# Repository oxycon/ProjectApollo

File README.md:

# ProjectApollo
This Github repository contains Designs/docs/software/PCB for Project Apollo (open source oxygen concentrator)

For more context behind the history/goals/motivation for this project please see our coverage in Helpful Engineering blog: 
- https://www.helpfulengineering.org/projects-news/project-spotlight-apollo-oxygen-concentrator/  

<b style='color:red'>Update</b>: check out our  presentation at RespiCon 2021! 
- https://github.com/oxycon/ProjectApollo/blob/master/docs/Project%20Apollo%20RespiCon%20v11.pdf

## Apollo v2 build instructions
- https://github.com/oxycon/ProjectApollo/blob/master/prototypes/Apollo%20v2/docs/Building%20instructions%20-%20prototype%20v2.pdf 

## Why
- Ventilators need oxygen! (typical FiO2 0.4 … 0.9)
- Oxygen generation is a big problem in developing countries. 
  - No established infrastructure. 
  - Oxygen bottles are expensive
- People are already looking at alternative (local) ways for producing oxygen
## What 
- Goal of the Apollo prototype = enabling people around the world to build the prototype as fast as possible
- Focus = Simplicity and speed of build 
- Final goal = Enable people to iterate and publish their own designs in the community
## How
- Follow the published build documentation
- Buy/source the materials (check out the BOM)
- Build the prototype
- Validate O2 concentration and flow. Use a good O2 and flow sensor. 
- Think about risk analysis and assessment: template for Apollo-derived design
- Document and iterate your own design. Publish your findings to the community! 

## Target 
- Output medical grade Oxygen ideally at 93% 
- Flow rate of 1-20 liters per minute (5 l/m being standard for oxygen therapy)

## Building instructions (prototype v2)
- Achieves O2 concentration out of the box: around 45% @ 5 liters/min (enough for less-critical ventilator use cases)
- Instructables-style (step-by-step) build instructions: https://github.com/oxycon/ProjectApollo/blob/master/prototypes/Apollo%20v2/docs/Building%20instructions%20-%20prototype%20v2.pdf 
- Bill of materials: https://github.com/oxycon/ProjectApollo/tree/master/prototypes/Apollo%20v2/BOM 

## Youtube videos
- Prototype v1 (old): https://www.youtube.com/playlist?list=PL34ykrB-qW7VGt1Hwd10Zb3s1eCDftkK8 
- Prototype v2 (latest): https://www.youtube.com/playlist?list=PL34ykrB-qW7X6d74_VnCFfBaVkm8pQXZK

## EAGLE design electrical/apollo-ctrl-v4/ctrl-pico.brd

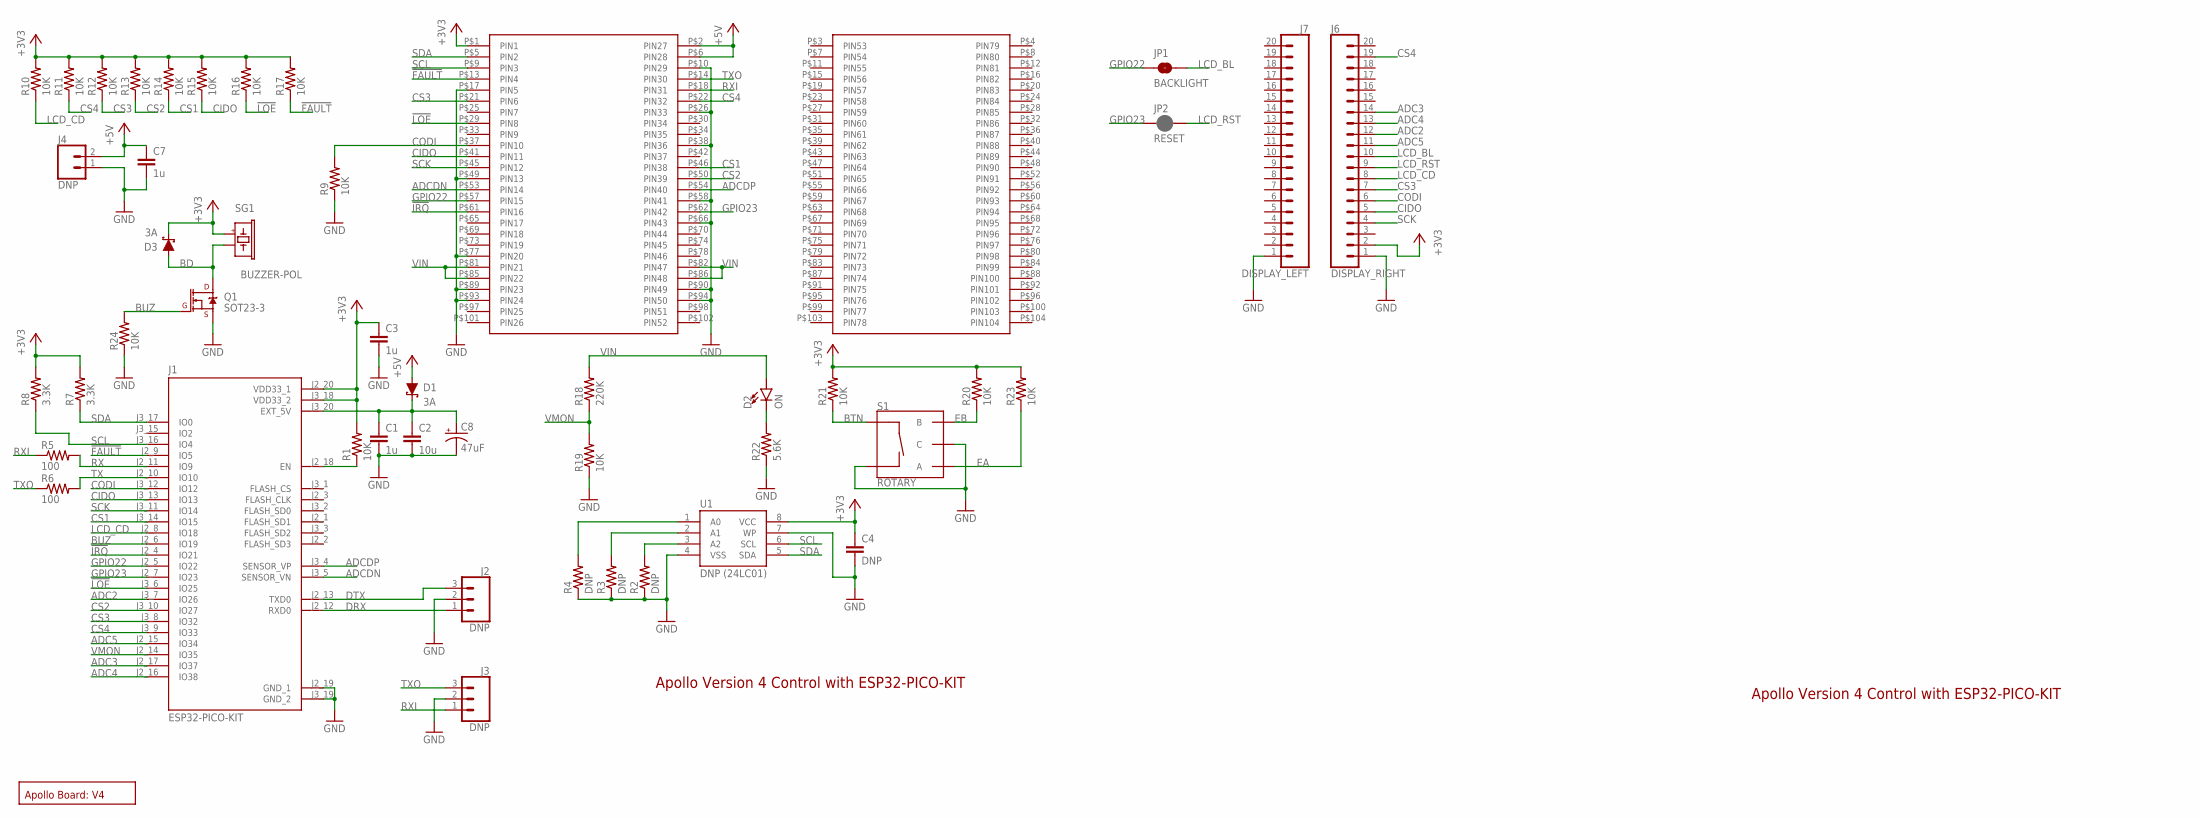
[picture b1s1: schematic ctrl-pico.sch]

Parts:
C1, C3, C7: 1u; 0805
C2: 10u; 0805
C4: DNP; 0805
C8: 47uF; PANASONIC_D
D1, D3: 3A; SMA-DIODE
D2: ON; LED-0603
J1: ESP32-PICO-KIT; XCVR_ESP32-PICO-KIT
J2, J3: DNP; 1X03
J4: DNP; 1X02
J6: DISPLAY_RIGHT; 1X20
J7: DISPLAY_LEFT; 1X20
JP1: BACKLIGHT; SMT-JUMPER_2_NO_NO-SILK
JP2: RESET; SMT-JUMPER_2_NC_PASTE_NO-SILK
Q1: SOT23-3
R1, R9, R10, R11, R12, R13, R14, R15, R16, R17, R19, R20, R21, R23, R24: 10K; 0805
R2, R3, R4: DNP; 0805
R5, R6: 100; 0805
R7, R8: 3.3K; 0805
R18: 220K; 0805
R22: 5.6K; 0805
S1: ROTARY; ROTARY_ENC_PLAIN
SG1: BUZZER-POL; BUZZER-SMT-4
U1: DNP (24LC01); SO08
U$1: PC104_CONNECTOR
U$2: BOARD_TEMPLATE1; BOARD_TEMPLATE

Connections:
!FAULT!: J1.J2_9 (IO5), R17.1, U$1.P$13 (PIN4)
!IRQ!: J1.J2_4 (IO21), U$1.P$61 (PIN16)
!LOE!: J1.J3_6 (IO25), R16.1, U$1.P$29 (PIN8)
+3V3: C3.1, C4.1, D3.C, J1.J2_20 (VDD33_1), J1.J3_18 (VDD33_2), J6.2, R1.2, R7.2, R8.2, R10.2, R11.2, R12.2, R13.2, R14.2, R15.2, R16.2, R17.2, R20.2, R21.2, R23.2, SG1.BP, U1.8 (VCC), U$1.P$1 (PIN1)
+5V: C7.1, D1.A, J4.2, U$1.P$2 (PIN27), U$1.P$6 (PIN28)
A0: R4.2, U1.1 (A0)
A1: R3.2, U1.2 (A1)
A2: R2.2, U1.3 (A2)
ADC2: J1.J3_7 (IO26), J6.12
ADC3: J1.J2_17 (IO37), J6.14
ADC4: J1.J2_16 (IO38), J6.13
ADC5: J1.J2_15 (IO34), J6.11
ADCDN: J1.J3_5 (SENSOR_VN), U$1.P$53 (PIN14)
ADCDP: J1.J3_4 (SENSOR_VP), U$1.P$54 (PIN40)
BD: D3.A, Q1.3 (D), SG1.BM (N)
BTN: R21.1, S1.SW+
BUZ: J1.J2_6 (IO19), Q1.1 (G), R24.2
CIDO: J1.J3_13 (IO13), J6.5, R15.1, U$1.P$41 (PIN11)
CODI: J1.J3_12 (IO12), J6.6, R9.2, U$1.P$37 (PIN10)
CS1: J1.J3_14 (IO15), R14.1, U$1.P$46 (PIN38)
CS2: J1.J3_10 (IO27), R13.1, U$1.P$50 (PIN39)
CS3: J1.J3_8 (IO32), J6.7, R12.1, U$1.P$21 (PIN6)
CS4: J1.J3_9 (IO33), J6.19, R11.1, U$1.P$22 (PIN32)
DRX: J1.J2_12 (RXD0), J2.1
DTX: J1.J2_13 (TXD0), J2.3
EA: R23.1, S1.A
EB: R20.1, S1.B
EN: J1.J2_18 (EN), R1.1
GND: C1.2, C2.2, C3.2, C4.2, C7.2, C8.-, J1.J2_19 (GND_1), J1.J3_19 (GND_2), J2.2, J3.2, J4.1, J6.1, J7.1, Q1.2 (S), R2.1, R3.1, R4.1, R9.1, R19.1, R22.1, R24.1, S1.C, S1.SW-, U1.4 (VSS), U1.7 (WP), U$1.P$10 (PIN29), U$1.P$17 (PIN5), U$1.P$26 (PIN33), U$1.P$38 (PIN36), U$1.P$49 (PIN13), U$1.P$58 (PIN41), U$1.P$66 (PIN43), U$1.P$77 (PIN20), U$1.P$89 (PIN23), U$1.P$90 (PIN49), U$1.P$93 (PIN24), U$1.P$94 (PIN50)
GPIO22: J1.J2_5 (IO22), JP1.1, U$1.P$57 (PIN15)
GPIO23: J1.J2_7 (IO23), JP2.1, U$1.P$62 (PIN42)
LCD_BL: J6.10, JP1.2
LCD_CD: J1.J2_8 (IO18), J6.8, R10.1
LCD_RST: J6.9, JP2.2
RX: J1.J2_11 (IO9), R5.2
RXI: J3.1, R5.1, U$1.P$18 (PIN31)
SCK: J1.J3_11 (IO14), J6.4, U$1.P$45 (PIN12)
SCL: J1.J3_16 (IO4), R8.1, U1.6 (SCL), U$1.P$9 (PIN3)
SDA: J1.J3_17 (IO0), R7.1, U1.5 (SDA), U$1.P$5 (PIN2)
TX: J1.J2_10 (IO10), R6.2
TXO: J3.3, R6.1, U$1.P$14 (PIN30)
USB5V: C1.1, C2.1, C8.+, D1.C, J1.J3_20 (EXT_5V)
VIN: D2.A, R18.2, U$1.P$81 (PIN21), U$1.P$82 (PIN47), U$1.P$85 (PIN22), U$1.P$86 (PIN48)
VLED: D2.C, R22.2
VMON: J1.J2_14 (IO35), R18.1, R19.2

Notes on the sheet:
Apollo Version 4 Control with ESP32-PICO-KIT

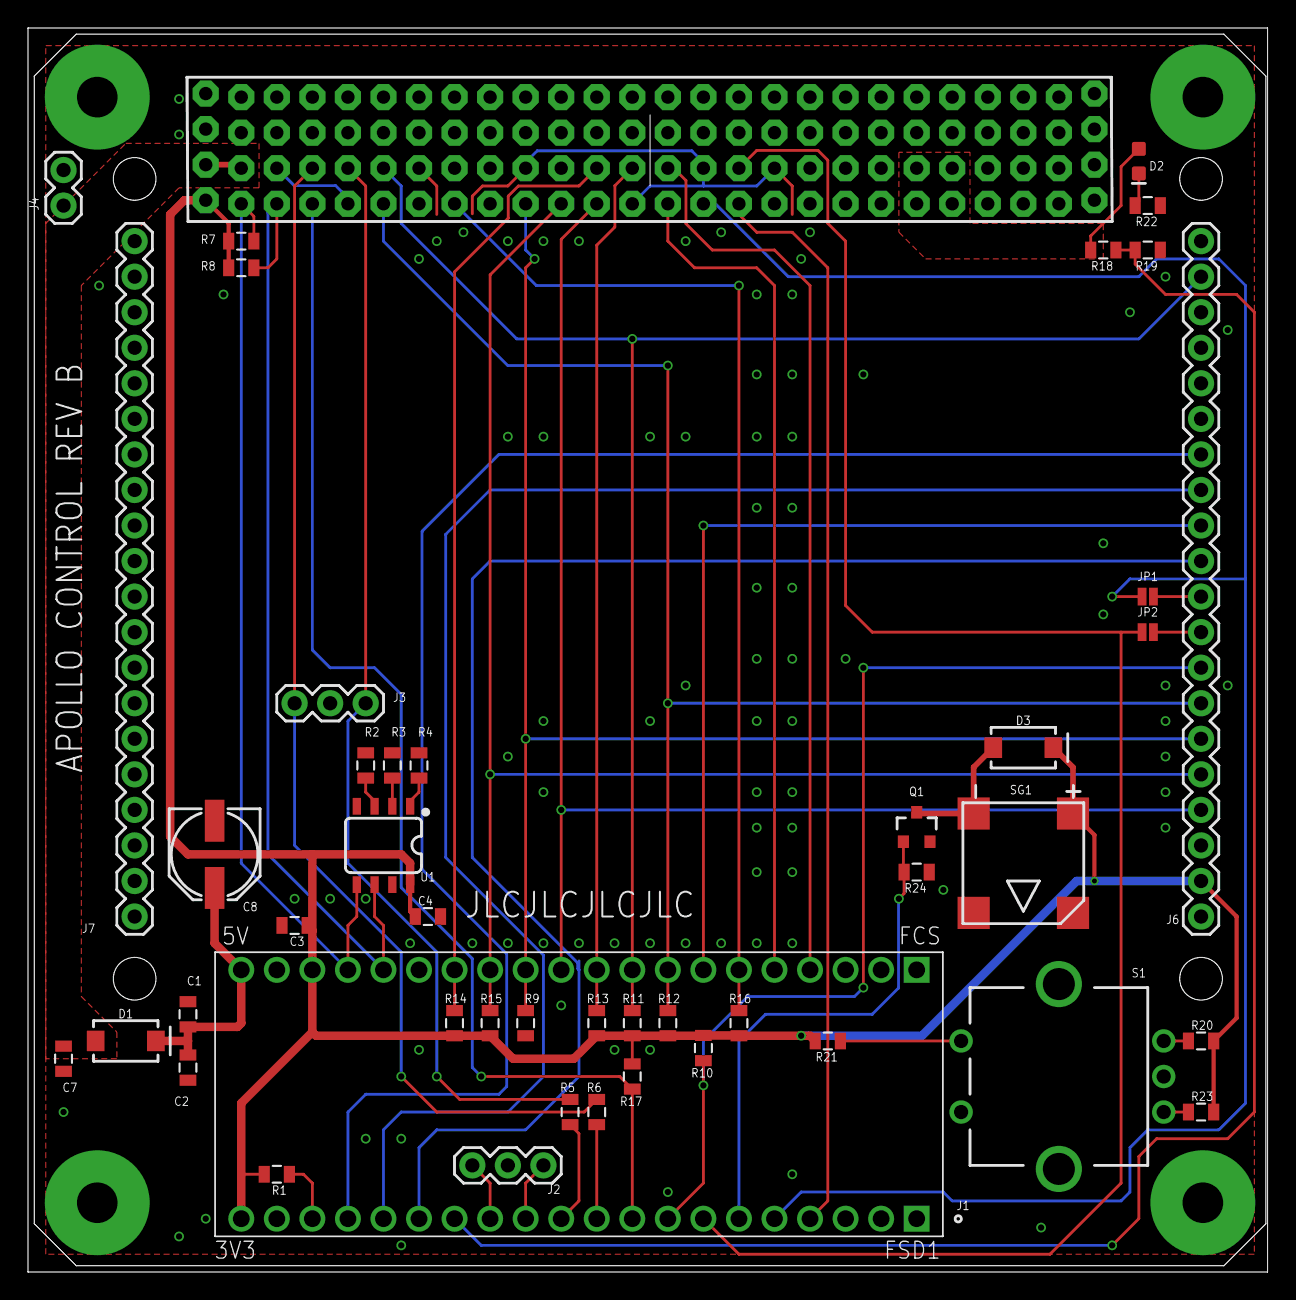
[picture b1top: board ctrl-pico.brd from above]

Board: 2 copper layers, 88.6 x 88.9 mm, 47 parts (0 on the bottom side), 45 nets.

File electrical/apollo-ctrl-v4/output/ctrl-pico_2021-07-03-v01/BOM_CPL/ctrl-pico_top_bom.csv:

Comment,Designator,Footprint,LCSC Part #
1u,C1 C3 C7,0805,
3.3K,R7 R8,0805,
3A,D1 D3,SMA-DIODE,
5.6K,R22,0805,
10K,R1 R9 R10 R11 R12 R13 R14 R15 R16 R17 R19 R20 R21 R23 R24,0805,
10u,C2,0805,
47uF,C8,PANASONIC_D,C134878
100,R5 R6,0805,
220K,R18,0805,
BACKLIGHT,JP1,SMT-JUMPER_2_NO_NO-SILK,
BUZZER-POL,SG1,BUZZER-SMT-4,
DNP,C4 R2 R3 R4,0805,
DNP (24LC01),U1,SO08,
ON,D2,LED-0603,
RESET,JP2,SMT-JUMPER_2_NC_PASTE_NO-SILK,
SOT23-3,Q1,SOT23-3,

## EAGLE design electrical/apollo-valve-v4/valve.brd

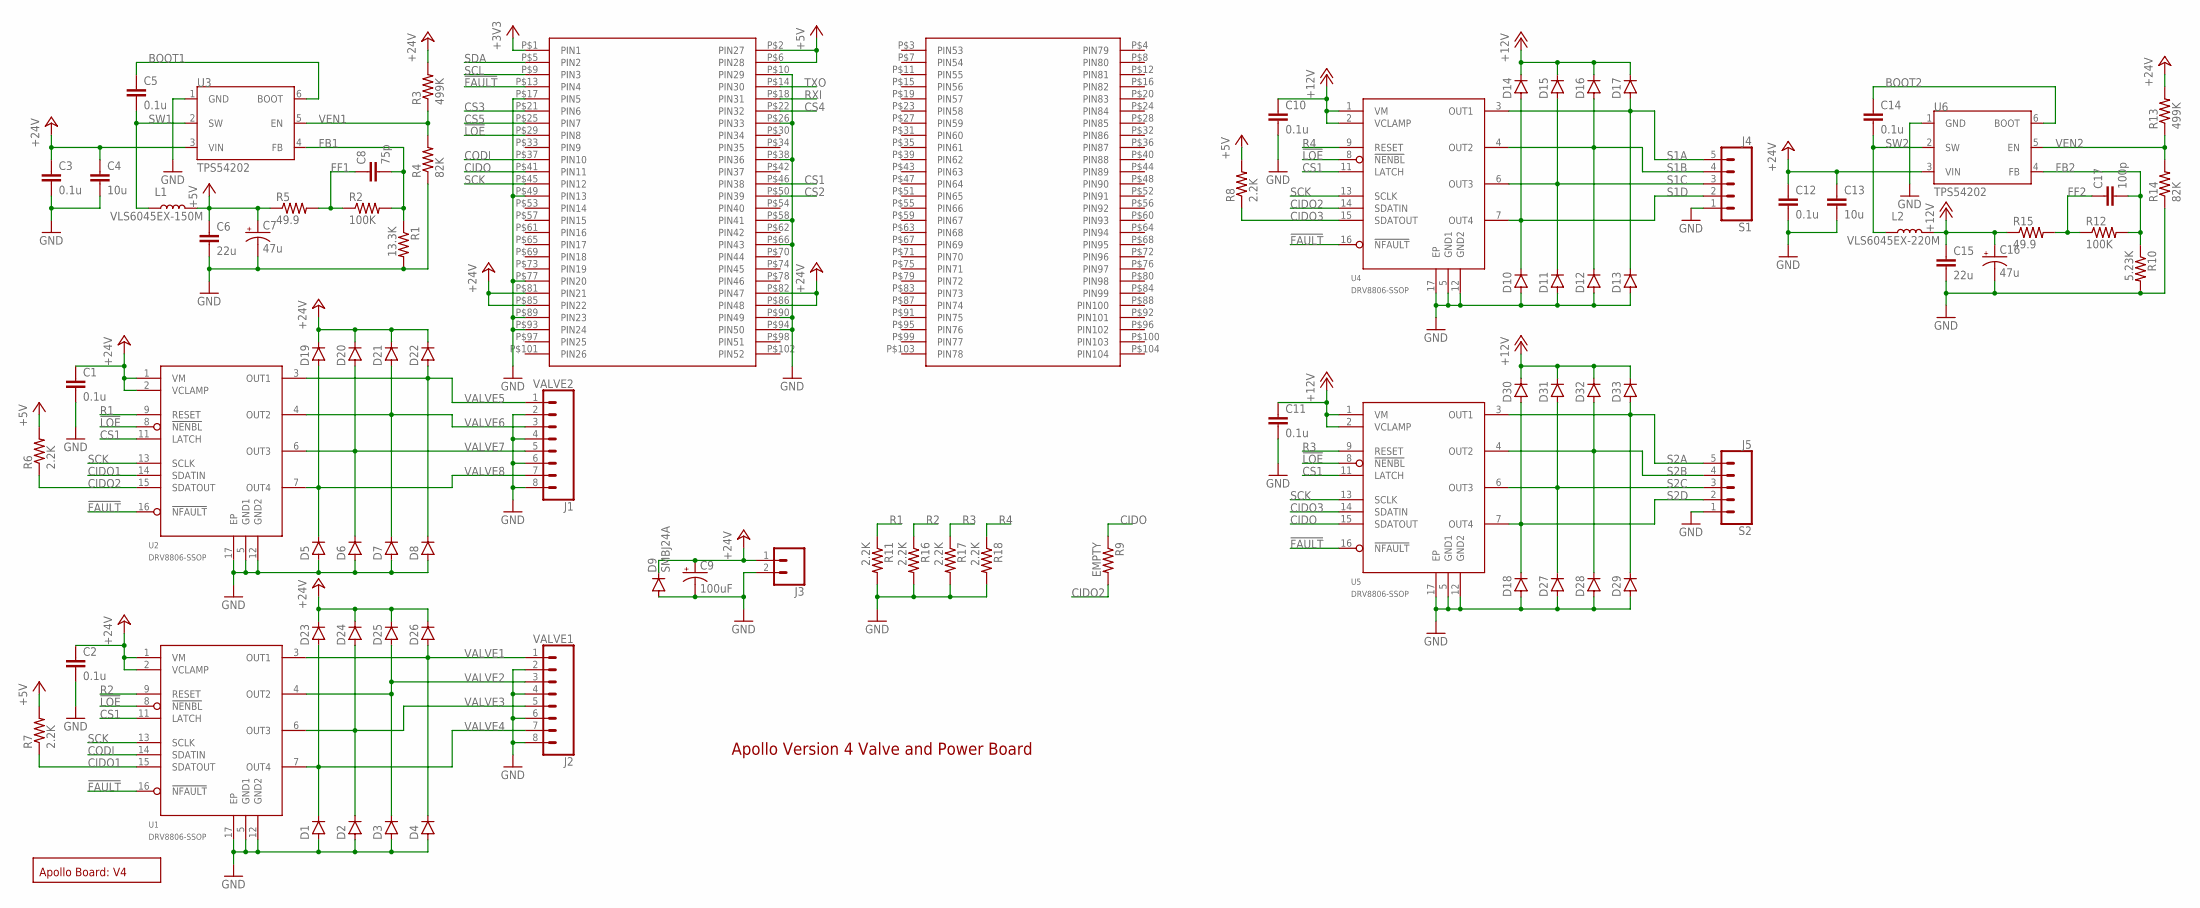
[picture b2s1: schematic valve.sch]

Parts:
C1, C2, C3, C5, C10, C11, C12, C14: 0.1u; 0805
C4, C13: 10u; 0805
C6, C15: 22u; 0805
C7, C16: 47u; PANASONIC_C
C8: 75p; 0805
C9: 100uF; PANASONIC_D
C17: 100p; 0805
D1, D2, D3, D4, D5, D6, D7, D8, D10, D11, D12, D13, D14, D15, D16, D17, D18, D19, D20, D21, D22, D23, D24, D25, D26, D27, D28, D29, D30, D31, D32, D33: B5819W; SOD123
D9: SMBJ24A; SMB
J1: VALVE2; SCREWTERMINAL-3.5MM-8
J2: VALVE1; SCREWTERMINAL-3.5MM-8
J3: CONN_023.5MM; SCREWTERMINAL-3.5MM-2
J4: S1; JST-5-PTH
J5: S2; JST-5-PTH
L1: VLS6045EX-150M; VLS6045EX
L2: VLS6045EX-220M; VLS6045EX
R1: 13.3K; 0805
R2, R12: 100K; 0805
R3, R13: 499K; 0805
R4, R14: 82K; 0805
R5, R15: 49.9; 0805
R6, R7, R8, R11, R16, R17, R18: 2.2K; 0805
R9: EMPTY; 0805
R10: 5.23K; 0805
U1, U2, U4, U5: DRV8806-SSOP; SOP65P640X120-17N
U3, U6: TPS54202; SOT23-6L
U$1: PC104_CONNECTOR
U$2: BOARD_TEMPLATE1; BOARD_TEMPLATE

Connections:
!FAULT!: U1.16 (!NFAULT), U2.16 (!NFAULT), U4.16 (!NFAULT), U5.16 (!NFAULT), U$1.P$13 (PIN4)
!LOE!: U1.8 (!NENBL), U2.8 (!NENBL), U4.8 (!NENBL), U5.8 (!NENBL), U$1.P$29 (PIN8)
+3V3: U$1.P$1 (PIN1)
+5V: C6.1, C7.+, L1.2, R5.1, R6.2, R7.2, R8.2, U$1.P$2 (PIN27), U$1.P$6 (PIN28)
+12V: C10.1, C11.1, C15.1, C16.+, D14.C, D15.C, D16.C, D17.C, D30.C, D31.C, D32.C, D33.C, L2.2, R15.1, U4.1 (VM), U4.2 (VCLAMP), U5.1 (VM), U5.2 (VCLAMP)
+24V: C1.1, C2.1, C3.1, C4.1, C9.+, C12.1, C13.1, D9.C, D19.C, D20.C, D21.C, D22.C, D23.C, D24.C, D25.C, D26.C, J3.1, R3.2, R13.2, U1.1 (VM), U1.2 (VCLAMP), U2.1 (VM), U2.2 (VCLAMP), U3.3 (VIN), U6.3 (VIN), U$1.P$81 (PIN21), U$1.P$82 (PIN47), U$1.P$85 (PIN22), U$1.P$86 (PIN48)
BOOT1: C5.1, U3.6 (BOOT)
BOOT2: C14.1, U6.6 (BOOT)
CIDO: R9.1, U5.15 (SDATOUT), U$1.P$41 (PIN11)
CIDO1: R7.1, U1.15 (SDATOUT), U2.14 (SDATIN)
CIDO2: R6.1, R9.2, U2.15 (SDATOUT), U4.14 (SDATIN)
CIDO3: R8.1, U4.15 (SDATOUT), U5.14 (SDATIN)
CODI: U1.14 (SDATIN), U$1.P$37 (PIN10)
CS1: U1.11 (LATCH), U2.11 (LATCH), U4.11 (LATCH), U5.11 (LATCH), U$1.P$46 (PIN38)
CS2: U$1.P$50 (PIN39)
CS3: U$1.P$21 (PIN6)
CS4: U$1.P$22 (PIN32)
CS5: U$1.P$25 (PIN7)
FB1: C8.2, R1.1, R2.2, U3.4 (FB)
FB2: C17.2, R10.1, R12.2, U6.4 (FB)
FF1: C8.1, R2.1, R5.2
FF2: C17.1, R12.1, R15.2
GND: C1.2, C2.2, C3.2, C4.2, C6.2, C7.-, C9.-, C10.2, C11.2, C12.2, C13.2, C15.2, C16.-, D1.A, D2.A, D3.A, D4.A, D5.A, D6.A, D7.A, D8.A, D9.A, D10.A, D11.A, D12.A, D13.A, D18.A, D27.A, D28.A, D29.A, J1.2, J1.4, J1.6, J1.8, J2.2, J2.4, J2.6, J2.8, J3.2, J4.1, J5.1, R1.2, R4.1, R10.2, R11.2, R14.1, R16.2, R17.2, R18.2, U1.5 (GND1), U1.12 (GND2), U1.17 (EP), U2.5 (GND1), U2.12 (GND2), U2.17 (EP), U3.1 (GND), U4.5 (GND1), U4.12 (GND2), U4.17 (EP), U5.5 (GND1), U5.12 (GND2), U5.17 (EP), U6.1 (GND), U$1.P$10 (PIN29), U$1.P$17 (PIN5), U$1.P$26 (PIN33), U$1.P$38 (PIN36), U$1.P$49 (PIN13), U$1.P$58 (PIN41), U$1.P$66 (PIN43), U$1.P$77 (PIN20), U$1.P$89 (PIN23), U$1.P$90 (PIN49), U$1.P$93 (PIN24), U$1.P$94 (PIN50)
R1: R11.1, U2.9 (RESET)
R2: R16.1, U1.9 (RESET)
R3: R17.1, U5.9 (RESET)
R4: R18.1, U4.9 (RESET)
RXI: U$1.P$18 (PIN31)
S1A: D13.C, D17.A, J4.5, U4.3 (OUT1)
S1B: D12.C, D16.A, J4.4, U4.4 (OUT2)
S1C: D11.C, D15.A, J4.3, U4.6 (OUT3)
S1D: D10.C, D14.A, J4.2, U4.7 (OUT4)
S2A: D29.C, D33.A, J5.5, U5.3 (OUT1)
S2B: D28.C, D32.A, J5.4, U5.4 (OUT2)
S2C: D27.C, D31.A, J5.3, U5.6 (OUT3)
S2D: D18.C, D30.A, J5.2, U5.7 (OUT4)
SCK: U1.13 (SCLK), U2.13 (SCLK), U4.13 (SCLK), U5.13 (SCLK), U$1.P$45 (PIN12)
SCL: U$1.P$9 (PIN3)
SDA: U$1.P$5 (PIN2)
SW1: C5.2, L1.1, U3.2 (SW)
SW2: C14.2, L2.1, U6.2 (SW)
TXO: U$1.P$14 (PIN30)
VALVE1: D4.C, D26.A, J2.1, U1.3 (OUT1)
VALVE2: D3.C, D25.A, J2.3, U1.4 (OUT2)
VALVE3: D2.C, D24.A, J2.5, U1.6 (OUT3)
VALVE4: D1.C, D23.A, J2.7, U1.7 (OUT4)
VALVE5: D8.C, D22.A, J1.1, U2.3 (OUT1)
VALVE6: D7.C, D21.A, J1.3, U2.4 (OUT2)
VALVE7: D6.C, D20.A, J1.5, U2.6 (OUT3)
VALVE8: D5.C, D19.A, J1.7, U2.7 (OUT4)
VEN1: R3.1, R4.2, U3.5 (EN)
VEN2: R13.1, R14.2, U6.5 (EN)

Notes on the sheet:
Apollo Version 4 Valve and Power Board

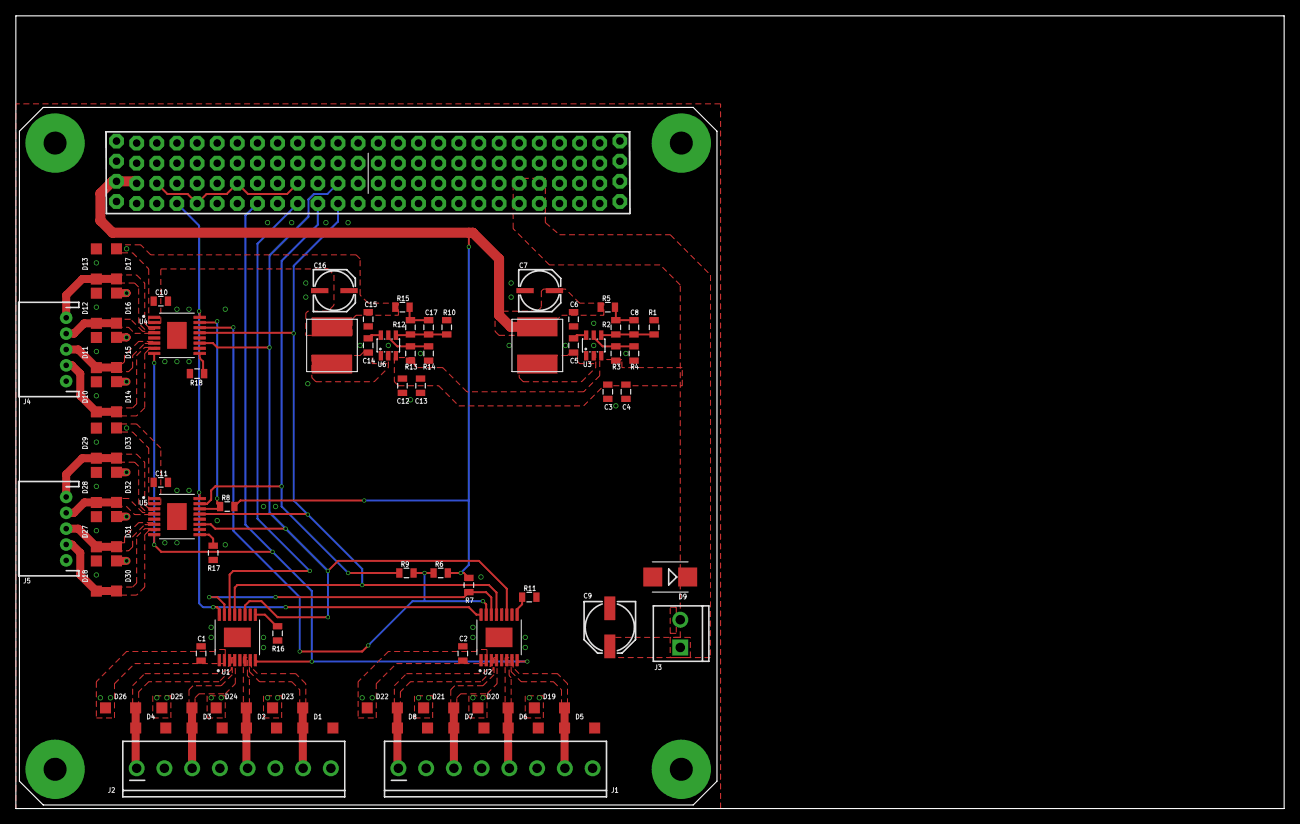
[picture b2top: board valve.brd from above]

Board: 4 copper layers, 160.0 x 100.0 mm, 83 parts (0 on the bottom side), 43 nets.

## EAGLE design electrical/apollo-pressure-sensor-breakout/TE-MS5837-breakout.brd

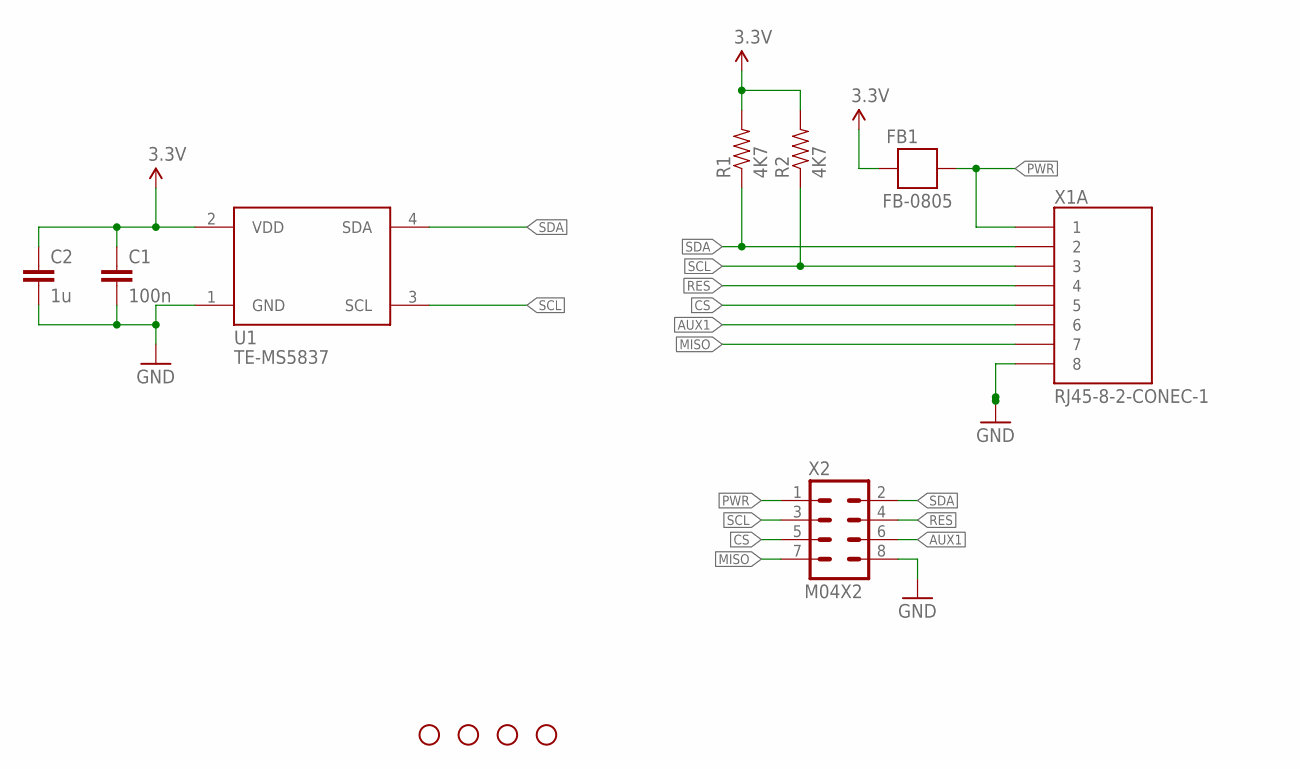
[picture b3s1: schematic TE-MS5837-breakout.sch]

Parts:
C1: 100n; 0805
C2: 1u; 0805
FB1: FB-0805; 0805
JP1, JP2, JP3, JP4: STAND-OFF
R1, R2: 4K7; 0805
U1: TE-MS5837
X1: RJ45-8-2-CONEC-1; CONEC-33TS3004ST-88001
X2: M04X2; 2X4

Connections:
3.3V: C1.1, C2.1, FB1.2, R1.2, R2.2, U1.2 (VDD)
AUX1: X1.6, X2.6
CS: X1.5, X2.5
GND: C1.2, C2.2, U1.1 (GND), X1.8, X1.M1, X1.M2, X2.8
MISO: X1.7, X2.7
PWR: FB1.1, X1.1, X2.1
RES: X1.4, X2.4
SCL: R2.1, U1.3 (SCL), X1.3, X2.3
SDA: R1.1, U1.4 (SDA), X1.2, X2.2

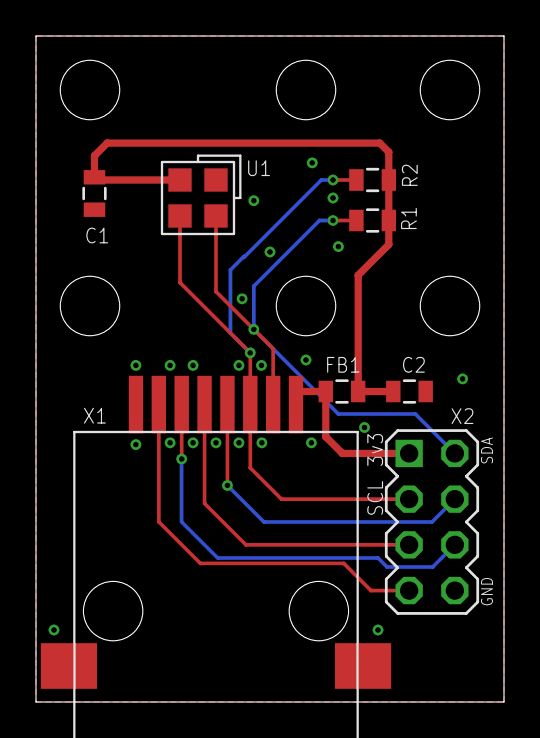
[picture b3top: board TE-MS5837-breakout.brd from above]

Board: 2 copper layers, 26.0 x 37.0 mm, 14 parts (0 on the bottom side), 9 nets.

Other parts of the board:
JP5, JP6: STAND-OFF

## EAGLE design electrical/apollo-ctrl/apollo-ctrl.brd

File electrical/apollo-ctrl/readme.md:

This is the circuit board for the main control circuit. The basic functions are:

 * Control all valves and fans
 * Monitor sensors
 * Monitor and alert for faults

The project is described and discussed in more detail here: https://docs.google.com/document/d/1zeXxTnBCQq67ddYeBdUPdo_KXUIRMmLPwQMJQMkbk8E/

The software used is Autodesk Eagle 9.

Please make your contributions on your own branches, as it's a nightmare merging changes to these files.

Please do not use default Eagle library components, add them to the local project .LBR file before adding them to the schematic. This ensures that everybody is using the same part and gives us the flexibility to fine tune the components.

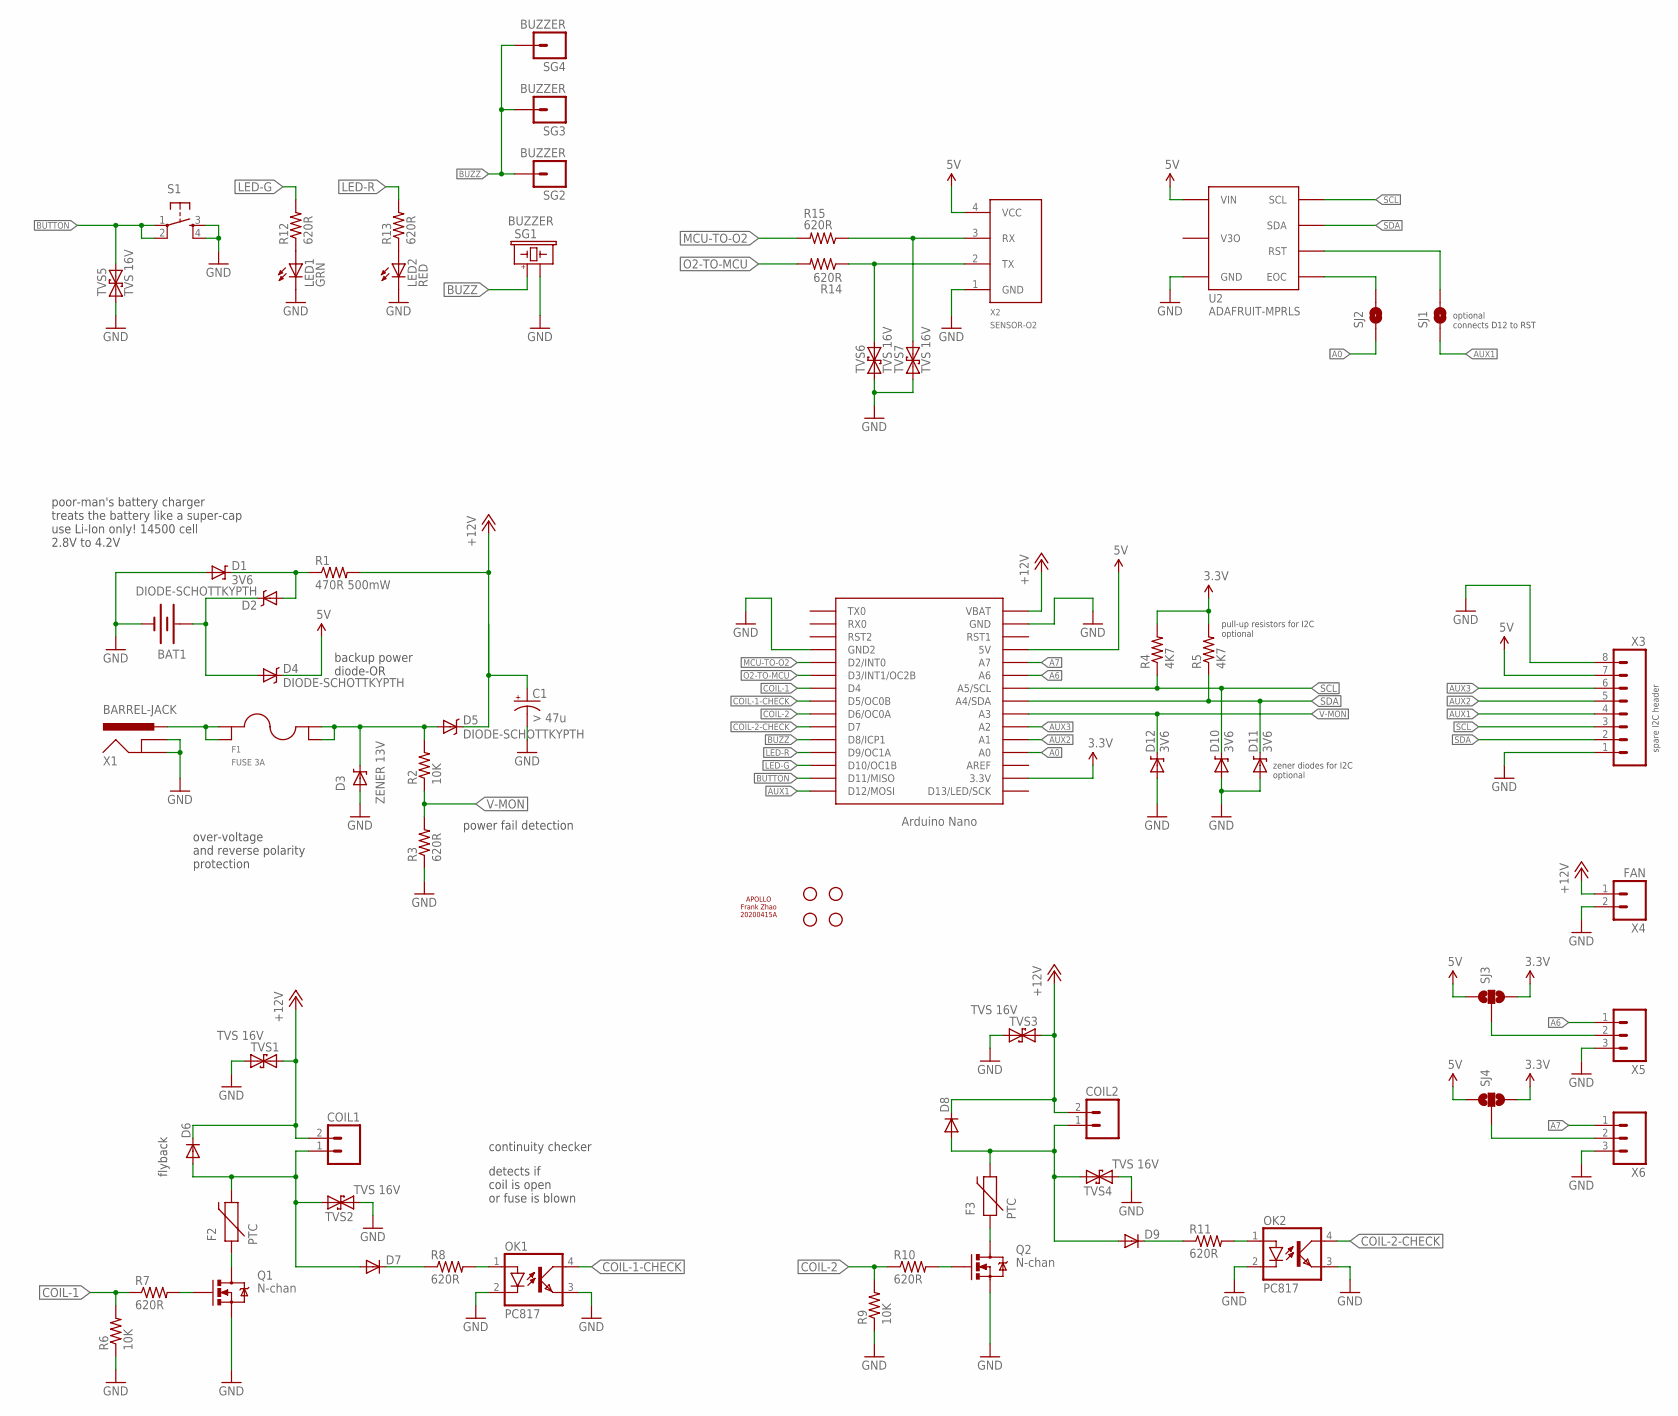
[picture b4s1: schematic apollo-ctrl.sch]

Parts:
BAT1: BATTERYAA-KIT; BATTERY-AA-KIT
C1: > 47u; CPOL-RADIAL-1000UF-25V
COIL1, COIL2: M023.5MM; SCREWTERMINAL-3.5MM-2
D1, D10, D11, D12: 3V6; DIODE-1N4148
D2, D4, D5: DIODE-SCHOTTKYPTH; DIODE-1N4001
D3: ZENER 13V; DO201-15
D6, D7, D8, D9: DIODE1N4148; DIODE-1N4148
F1: FUSE 3A; FUSE-KEYSTONE-3568
F2, F3: PTC
JP1, JP2, JP3, JP4: STAND-OFF
LED1: GRN; LED5MM
LED2: RED; LED5MM
LOGO1: APOLLO-LOGO
OK1, OK2: PC817; DIL04
Q1, Q2: N-chan; TO220V
R1: 470R 500mW; AXIAL-0.5
R2, R6, R9: 10K; AXIAL-0.4
R3, R7, R8, R10, R11, R12, R13, R14, R15: 620R; AXIAL-0.4
R4, R5: 4K7; AXIAL-0.4
S1: TAC_SWITCHPTH; TACTILE-PTH
SG1: BUZZER; BUZZER-AI-3035
SG2, SG3, SG4: BUZZER; 1X01NS
SJ1, SJ2: SOLDERJUMPERNO; SJ_2S-NO
SJ3, SJ4: SOLDERJUMPER_2WAYS; SJ_3
TVS1, TVS2, TVS3, TVS4, TVS5, TVS6, TVS7: TVS 16V; DIODE-1N4148
U1: NANO
U2: ADAFRUIT-MPRLS
X1: BARREL-JACK; POWER_JACK_PTH
X2: SENSOR-O2; JST-PH-4-VERT
X3: M081X08; 1X08
X4: FAN; 1X02
X5, X6: M03PTH; 1X03

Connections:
3.3V: R4.P$2 (2), R5.P$2 (2), SJ3.3, SJ4.3, U1.3.3V
5V: D4.C, SJ3.1, SJ4.1, U1.5V, U2.VIN, X2.4 (VCC), X3.7
+12V: C1.1 (+), COIL1.2, COIL2.2, D5.C, D6.C, D8.C, R1.P$2 (2), TVS1.C, TVS3.C, U1.RAW (VBAT), X4.1
A0: SJ2.1, U1.A0
A6: U1.A6, X5.1
A7: U1.A7, X6.1
AUX1: SJ1.1, U1.D12 (D12/MOSI), X3.4
AUX2: U1.A1, X3.5
AUX3: U1.A2, X3.6
BUTTON: S1.1, S1.2, TVS5.C, U1.D11 (D11/MISO)
BUZZ: SG1.P, SG2.1, SG3.1, SG4.1, U1.D8 (D8/ICP1)
COIL-1: R6.P$2 (2), R7.P$1 (1), U1.D4
COIL-1-CHECK: OK1.4 (COL), U1.D5 (D5/OC0B)
COIL-2: R9.P$2 (2), R10.P$1 (1), U1.D6 (D6/OC0A)
COIL-2-CHECK: OK2.4 (COL), U1.D7
GND: BAT1.GND@1 (-), C1.2 (-), D1.A, D3.A, D10.A, D11.A, D12.A, LED1.K (C), LED2.K (C), OK1.2 (C), OK1.3 (EMIT), OK2.2 (C), OK2.3 (EMIT), Q1.3 (S), Q2.3 (S), R3.P$1 (1), R6.P$1 (1), R9.P$1 (1), S1.3, S1.4, SG1.N, TVS1.A, TVS2.A, TVS3.A, TVS4.A, TVS5.A, TVS6.A, TVS7.A, U1.GND, U1.GND1 (GND2), U2.GND, X1.GND, X1.GNDBREAK, X2.1 (GND), X3.1, X3.8, X4.2, X5.3, X6.3
LED-G: R12.P$2 (2), U1.D10 (D10/OC1B)
LED-R: R13.P$2 (2), U1.D9 (D9/OC1A)
MCU-TO-O2: R15.P$2 (2), U1.D2 (D2/INT0)
unnamed: SJ1.2, U2.RST
unnamed: F2.1, Q1.2 (D)
unnamed: Q1.1 (G), R7.P$2 (2)
unnamed: OK1.1 (A), R8.P$2 (2)
unnamed: COIL1.1, D6.A, D7.A, F2.2, TVS2.C
unnamed: F1.1A, F1.1B, X1.PWR
unnamed: D7.C, R8.P$1 (1)
unnamed: OK2.1 (A), R11.P$2 (2)
unnamed: Q2.1 (G), R10.P$2 (2)
unnamed: COIL2.1, D8.A, D9.A, F3.2, TVS4.C
unnamed: F3.1, Q2.2 (D)
unnamed: D9.C, R11.P$1 (1)
unnamed: D3.C, D5.A, F1.2A, F1.2B, R2.P$2 (2)
unnamed: BAT1.PWR@1 (+), D2.C, D4.A
unnamed: LED2.A, R13.P$1 (1)
unnamed: LED1.A, R12.P$1 (1)
unnamed: R14.P$1 (1), TVS6.C, X2.2 (TX)
unnamed: R15.P$1 (1), TVS7.C, X2.3 (RX)
unnamed: D1.C, D2.A, R1.P$1 (1)
unnamed: SJ2.2, U2.EOC
unnamed: SJ4.2, X6.2
unnamed: SJ3.2, X5.2
O2-TO-MCU: R14.P$2 (2), U1.D3 (D3/INT1/OC2B)
SCL: D10.C, R4.P$1 (1), U1.A5 (A5/SCL), U2.SCL, X3.3
SDA: D11.C, R5.P$1 (1), U1.A4 (A4/SDA), U2.SDA, X3.2
V-MON: D12.C, R2.P$1 (1), R3.P$2 (2), U1.A3

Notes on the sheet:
poor-man's battery charger treats the battery like a super-cap use Li-Ion only! 14500 cell 2.8V to 4.2V
continuity checker
power fail detection
backup power diode-OR
over-voltage and reverse polarity protection
flyback
detects if coil is open or fuse is blown
spare I2C header
zener diodes for I2C optional
pull-up resistors for I2C optional
optional connects D12 to RST

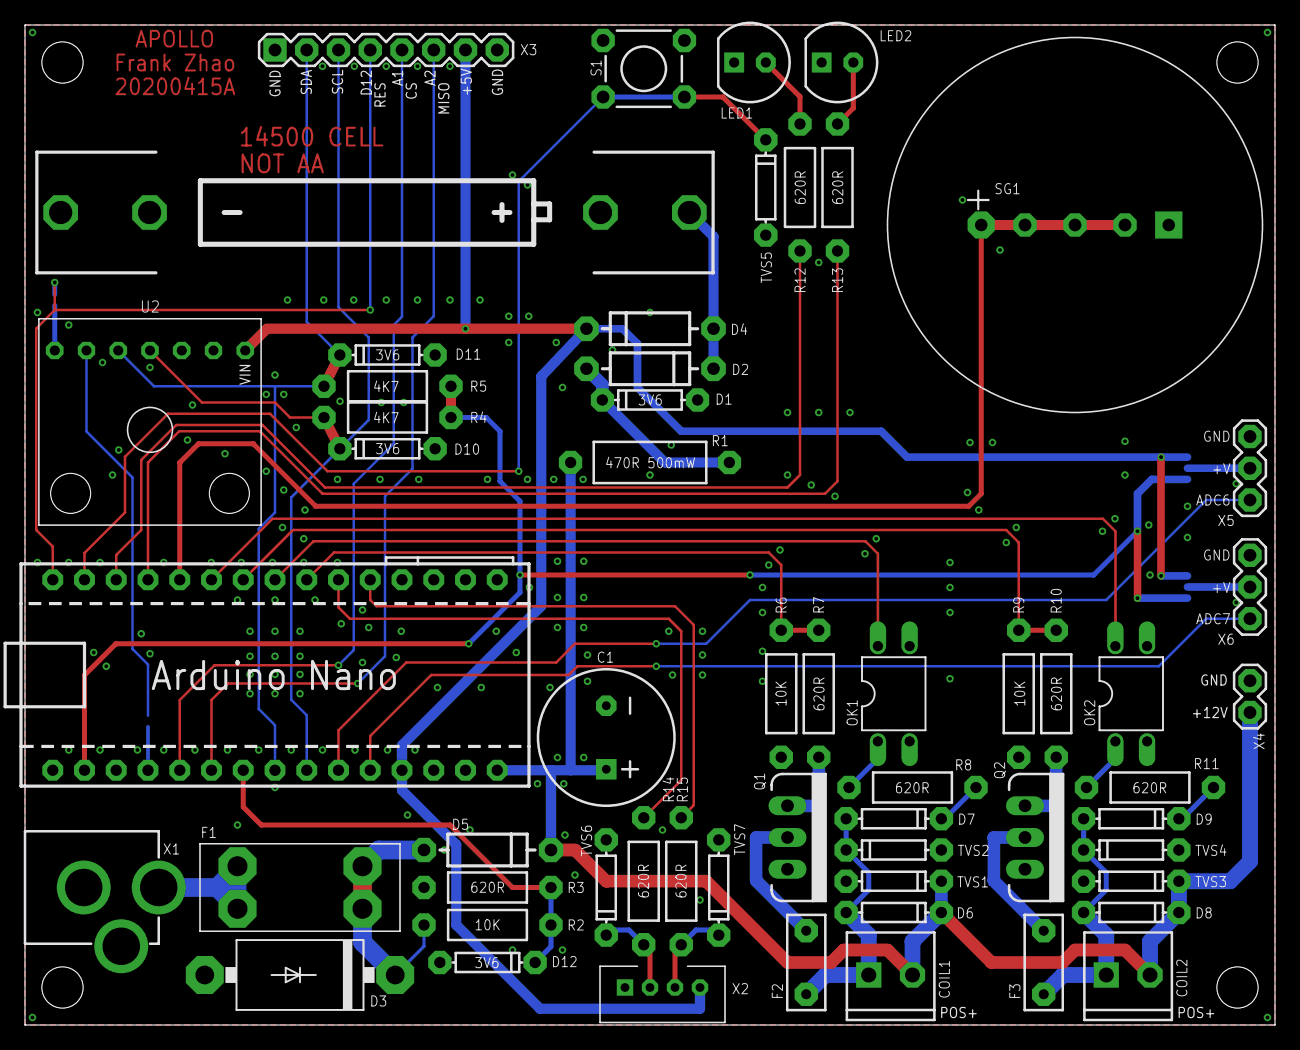
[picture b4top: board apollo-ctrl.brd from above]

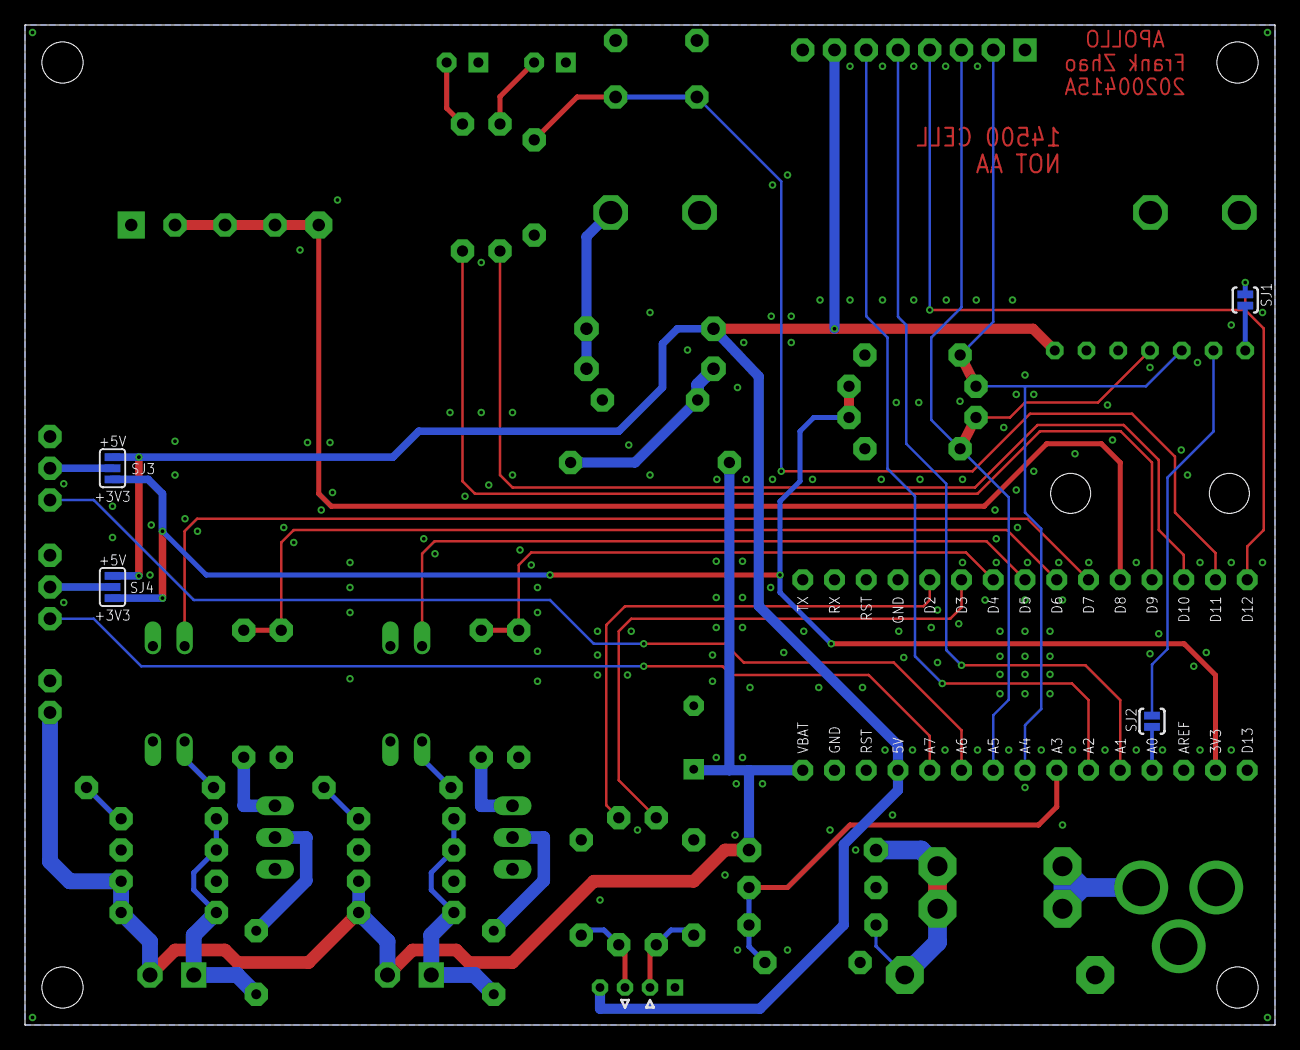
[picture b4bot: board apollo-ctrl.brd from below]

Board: 2 copper layers, 100.0 x 80.0 mm, 69 parts (4 on the bottom side), 45 nets.

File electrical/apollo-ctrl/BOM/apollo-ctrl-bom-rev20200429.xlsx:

Qty | Des | Name | Value | Rating | Footprint |  | Digi-Key
1 | C1 | capacitor, electrolytic | 47uF | 25V | TH, 5mm pitch, 11mm dia |  | https://www.digikey.com/short/zzb82b
2 | COIL1, COIL2 | terminal block |  |  | TH, 3.5mm |  | https://www.digikey.com/short/zzb8w4
4 | D1, D10, D11, D12 | diode, zener | 3.6V | 500mW | TH, DO-35 |  | https://www.digikey.com/short/zzb8n2
3 | D2, D4, D5 | diode, schottky |  |  | TH, DO-15 |  | https://www.digikey.com/short/zzb8vq
1 | D3 | diode, zener | 13V | 5W | TH, DO-201 |  | https://www.digikey.com/product-detail/en/central-semiconduc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
4 | D6, D7, D8, D9 | diode | 1N4148 |  | TH, DO-35 |  | https://www.digikey.com/short/zzb81w
1 | F1 | fuse holder |  |  | TH |  | https://www.digikey.com/product-detail/en/keystone-electroni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
1 | F1 | fuse | 3A |  |  |  | https://www.digikey.com/short/zzbj7z
1 | LED1 | LED | green |  | TH, 5mm |  | https://www.digikey.com/short/zzbjb4
1 | LED2 | LED | red |  | TH, 5mm |  | https://www.digikey.com/short/zzbjb5
2 | F2, F3 | fuse, PTC |  |  |  |  | https://www.digikey.com/product-detail/en/littelfuse-inc/RHE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
2 | OK1, OK2 | optocoupler | 817 |  | TH, DIP |  | https://www.digikey.com/short/zzbj33
2 | Q1, Q2 | MOSFET | N-chan | 1A, 20V | TO-220 |  | https://www.digikey.com/short/zzbjq4
1 | R1 | resistor | 470Ω | 500mW | TH |  | https://www.digikey.com/short/zzbjjh
7 | TVS | diode, TVS | 16V |  | DO-15 |  | https://www.digikey.com/product-detail/en/littelfuse-inc/P6K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
1 | SG1 | buzzer | 3V |  | TH |  | https://www.digikey.com/product-detail/en/pui-audio-inc/AI-3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
1 | X1 | power jack |  |  | TH |  | https://www.digikey.com/product-detail/en/cui-devices/PJ-002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
8 | R7, R8, R10, R11, R12, R13, R14, R15 | resistor | 620Ω | 0.25W | TH |  | https://www.digikey.com/short/zzbjht
2 | R4, R5 | resistor | 4.7kΩ | 0.25W | TH |  | https://www.digikey.com/short/zzbjhq
3 | R2, R6, R9 | resistor | 10kΩ | 0.25W | TH |  | https://www.digikey.com/short/zzbjhj

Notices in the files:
electrical/components/NANO33IoTV2.0.brd:
Copyright (c) 2016-2017 Arduino LLC.  All right reserved. EAGLE Design Rules
parts and their libraries:
SparkFun-DiscreteSemi: Licensing: Creative Commons ShareAlike 4.0 International - https://creativecommons.org/licenses/by-sa/4.0
Arduino-utility: This work is licensed under a Creative Commons Attribution-ShareAlike 4.0 International License.
